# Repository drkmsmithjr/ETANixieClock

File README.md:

# [Estimated Time of Arrival (ETA) Nixie Tube Clock](http://surfncircuits.com/2018/04/01/what-is-an-eta-nixie-tube-clock-and-how-do-you-build-one)
This DIY project will combine the estimated time of arrival function with a nixie tube display to create an estimated time of arrival (ETA) Nixie tube clock. It is all easily controlled by a Raspberry Pi Zero W that is connected to the internet through WiFi to provide the latest time and gets the ETA for any number of destinations. The travel time is provided by the free Google Directions API interface that includes traffic to give the best estimates on any particular day.   The goal is that with an ETA Nixie tube clock, no math is needed to add a rough, often optimistic travel time, to the actual time to determine if we are running late.   The clock does that for you and with the power of IOT, is much more accurate!    A motion sensor is also added to the clock to turn off the Nixie Tube Display when no one is around, saving power and increasing the nixie tube lifetime.    The complete project, including the six IN-4 Nixie tubes, are powered from a 1 amp iPhone charger using the 5v to 170v Nixie Tube Power supply described in another repository. 

See [www.surfncircuits.com](http://surfncircuits.com/2018/04/01/what-is-an-eta-nixie-tube-clock-and-how-do-you-build-one)  for a complete description.  This github repository contains the Kicad Schematic, Spice Simulation, Efficiency Calculations of the Estimated Time of Arrival (ETA) Nixie Tube Clock.   

__ETANixieCode__:  This is the python code that will be placed in the ETANixieClock directory on the Raspberry Pi zero.    

__KC_ETAclock-5v__:  KiCad schematic, PCB Layout, BOM of the ETA Nixie tube clock.  You can order the PCB from oshPark at <a href="https://oshpark.com/shared_projects/B9CmGCXJ"></img></a>  

__SimCalcFiles__:  Spice simulation files of the Nixie Tube bi-quinary driving circuit.    

__Datasheeets__: Datasheets for the pinout and the TPIC6B595.  In the Kicad Schematic, the part numbers and Digikey (TM) links are listed already.   Also the complete BOM is located in the KC-ETAclock-5v Directory (ETAclock_BOM.ods).      

See the complete blogs entry at  [www.surfncircuits.com](http://surfncircuits.com/2018/04/01/what-is-an-eta-nixie-tube-clock-and-how-do-you-build-one)

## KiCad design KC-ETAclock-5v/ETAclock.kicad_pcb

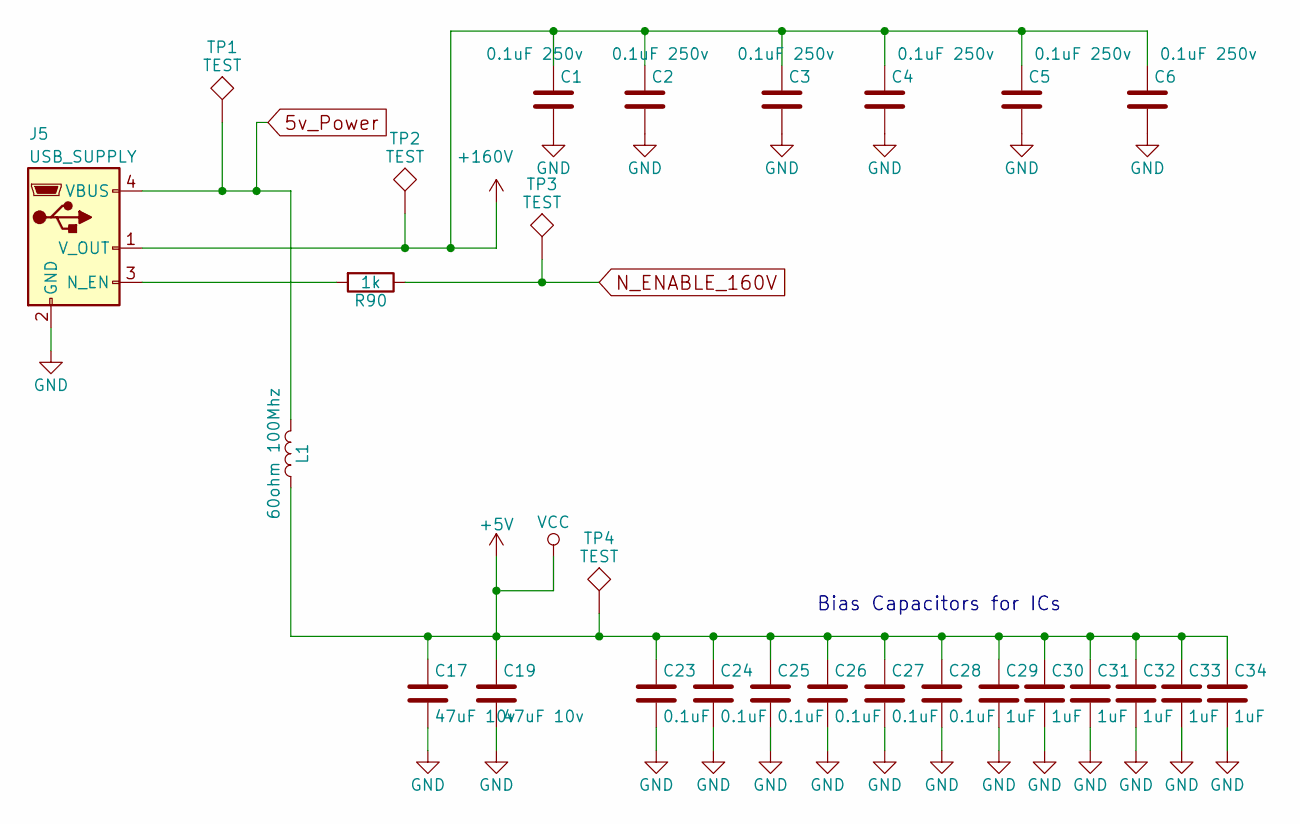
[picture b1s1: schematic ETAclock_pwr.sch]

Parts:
C1, C2, C3, C4, C5, C6: 0.1uF 250v; C_0805; MPN CGA4J3X7T2E104M125AE
C17, C19: 47uF 10v; C_0805; MPN LMK212BBJ476MG-T
C23, C24, C25, C26, C27, C28: 0.1uF; C_0805
C29, C30, C31, C32, C33, C34: 1uF; C_0805
J5: USB_SUPPLY; USB_SUPPLY_5v_TO_170v_MINI_2M
L1: 60ohm 100Mhz; R_0805; MPN BKP2125HS600-T
R90: 1k; R_0805
TP1, TP2, TP3, TP4: TEST; PINTST

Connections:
5v_Power: J5.4 (VBUS), L1.2, TP1.1
+5V: C17.1, C19.1, C23.1, C24.1, C25.1, C26.1, C27.1, C28.1, C29.1, C30.1, C31.1, C32.1, C33.1, C34.1, L1.1, TP4.1; also elsewhere on the board
+160V: C1.1, C2.1, C3.1, C4.1, C5.1, C6.1, J5.1 (V_OUT), TP2.1; also elsewhere on the board
GND: C1.2, C2.2, C3.2, C4.2, C5.2, C6.2, C17.2, C19.2, C23.2, C24.2, C25.2, C26.2, C27.2, C28.2, C29.2, C30.2, C31.2, C32.2, C33.2, C34.2, J5.2 (GND); also elsewhere on the board
N_ENABLE_160V: R90.1, TP3.1; also elsewhere on the board
unnamed: J5.3 (N_EN), R90.2

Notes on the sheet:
Bias Capacitors for ICs

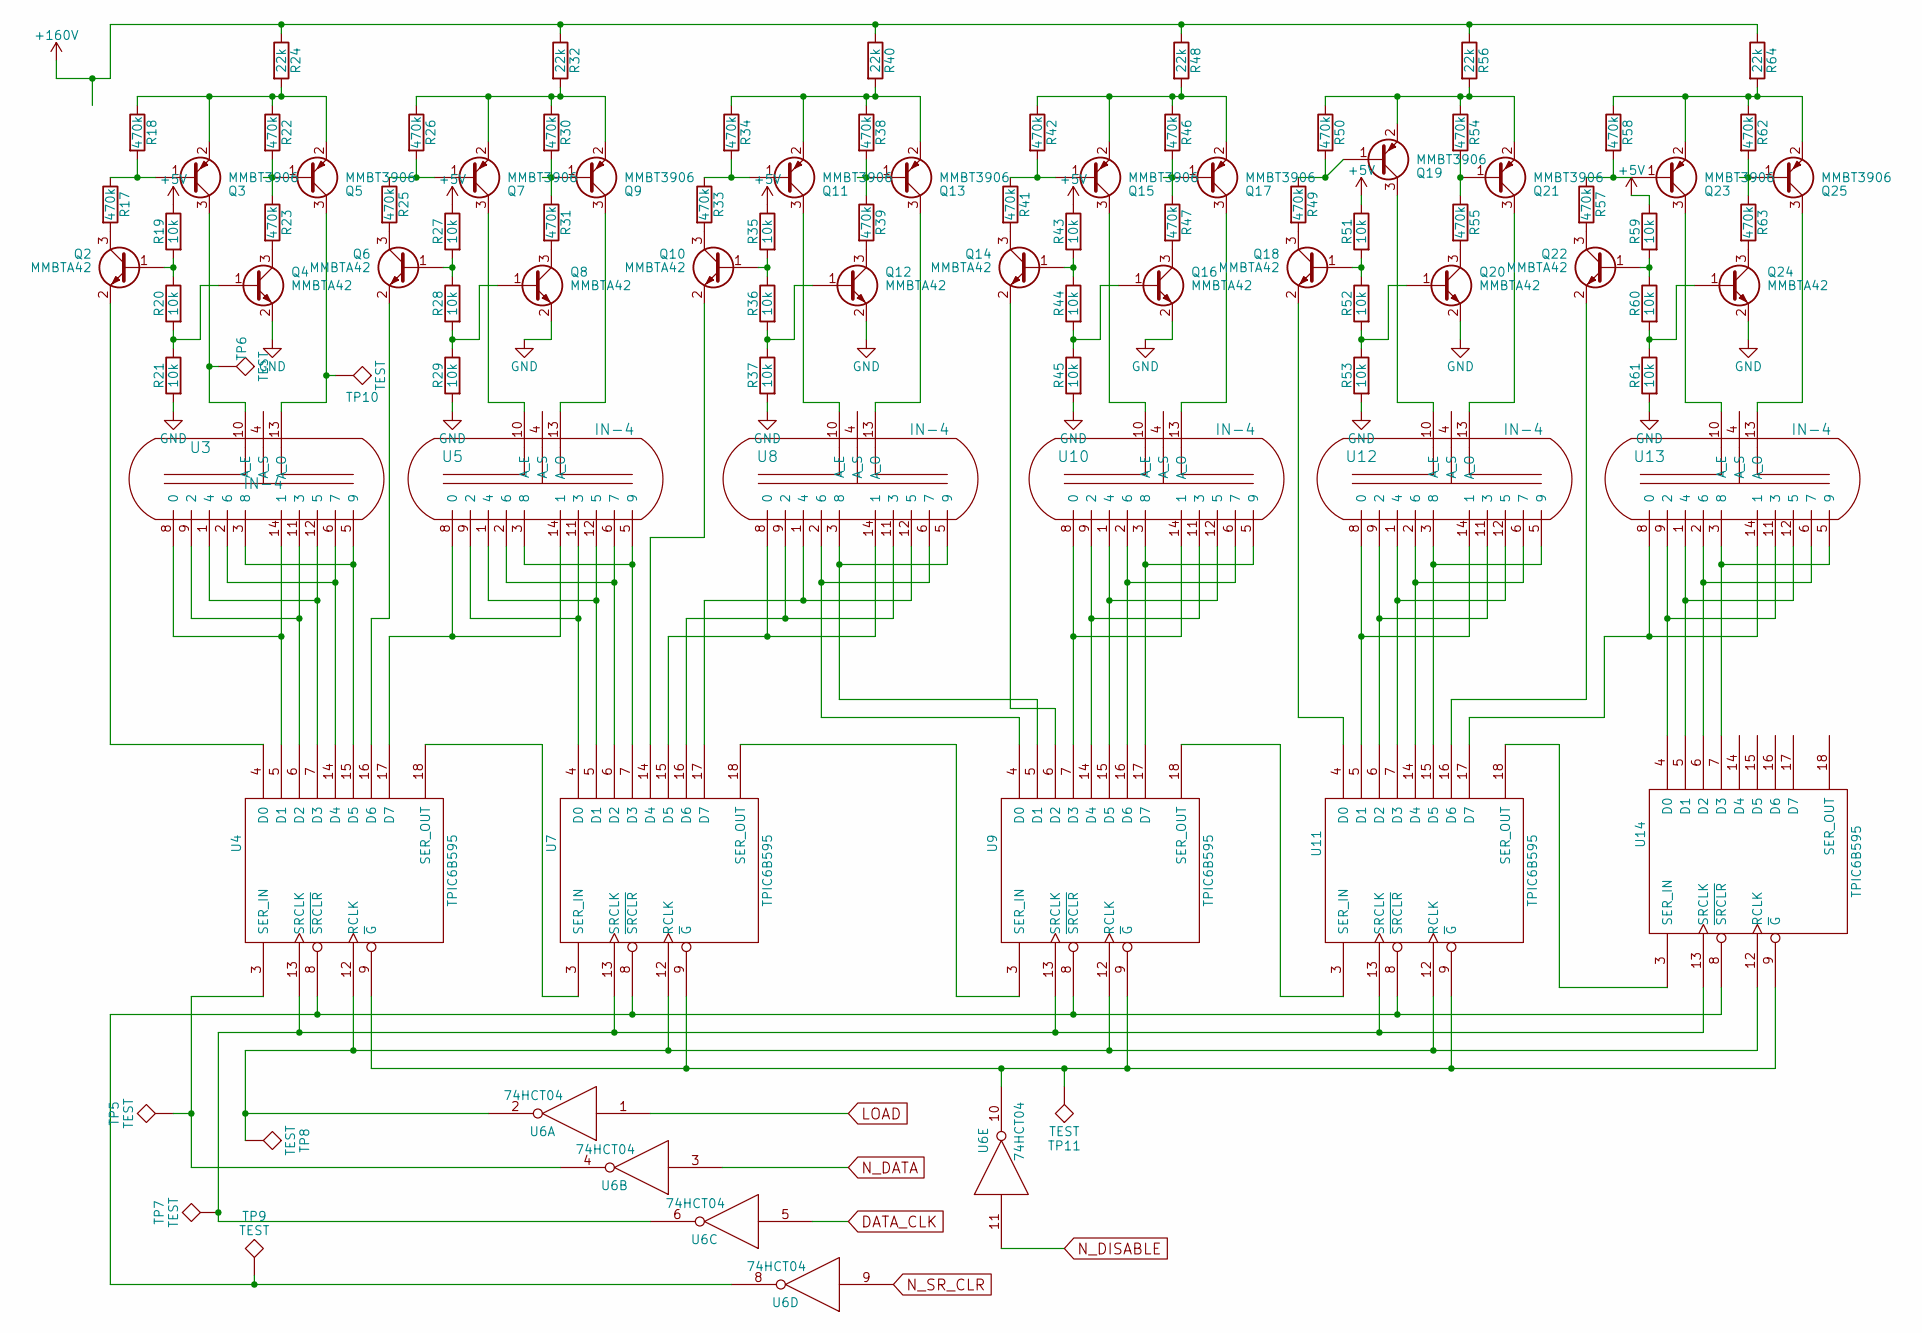
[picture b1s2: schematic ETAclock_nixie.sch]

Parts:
Q2, Q4, Q6, Q8, Q10, Q12, Q14, Q16, Q18, Q20, Q22, Q24: MMBTA42; SOT-23; MPN MMBTA42-TP
Q3, Q5, Q7, Q9, Q11, Q13, Q15, Q17, Q19, Q21, Q23, Q25: MMBT3906; SOT-23; MPN MMBTA92-TP
R17, R18, R22, R23, R25, R26, R30, R31, R33, R34, R38, R39, R41, R42, R46, R47, R49, R50, R54, R55, R57, R58, R62, R63: 470k; R_0805
R19, R20, R21, R27, R28, R29, R35, R36, R37, R43, R44, R45, R51, R52, R53, R59, R60, R61: 10k; R_0805
R24, R32, R40, R48, R56, R64: 22k; R_0805
TP5, TP6, TP7, TP8, TP9, TP10, TP11: TEST; PINTST
U3, U5, U8, U10, U12, U13: IN-4
U4, U7, U9, U11, U14: TPIC6B595; SOIC-20W_7.5x12.8mm_Pitch1.27mm; MPN TPIC6B595DWR
U6: 74HCT04; SOIC-14_3.9x8.7mm_Pitch1.27mm; MPN MM74HCT04MX

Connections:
+5V: R19.1, R27.1, R35.1, R43.1, R51.1, R59.1, U4.2 (VCC), U6.14 (VCC), U7.2 (VCC), U9.2 (VCC), U11.2 (VCC), U14.2 (VCC); also elsewhere on the board
+160V: R24.1, R32.1, R40.1, R48.1, R56.1, R64.1; also elsewhere on the board
DATA_CLK: U6.5; also elsewhere on the board
GND: Q4.2 (E), Q8.2 (E), Q12.2 (E), Q16.2 (E), Q20.2 (E), Q24.2 (E), R21.2, R29.2, R37.2, R45.2, R53.2, R61.2, U4.10 (GND), U4.11 (GND), U4.19 (GND), U6.7 (GND), U7.10 (GND), U7.11 (GND), U7.19 (GND), U9.10 (GND), U9.11 (GND), U9.19 (GND), U11.10 (GND), U11.11 (GND), U11.19 (GND), U14.10 (GND), U14.11 (GND), U14.19 (GND); also elsewhere on the board
LOAD: U6.1; also elsewhere on the board
N_DATA: U6.3; also elsewhere on the board
N_DISABLE: U6.11; also elsewhere on the board
N_SR_CLR: U6.9; also elsewhere on the board
unnamed: Q2.1 (B), R19.2, R20.1
unnamed: Q2.2 (E), U4.4 (D0)
unnamed: Q2.3 (C), R17.2
unnamed: Q3.1 (B), R17.1, R18.2
unnamed: Q3.2 (E), Q5.2 (E), R18.1, R22.1, R24.2
unnamed: Q3.3 (C), TP6.1, U3.10 (A_E)
unnamed: Q4.1 (B), R20.2, R21.1
unnamed: Q4.3 (C), R23.2
unnamed: Q5.1 (B), R22.2, R23.1
unnamed: Q5.3 (C), TP10.1, U3.13 (A_O)
unnamed: Q6.1 (B), R27.2, R28.1
unnamed: Q6.2 (E), U4.16 (D6)
unnamed: Q6.3 (C), R25.2
unnamed: Q7.1 (B), R25.1, R26.2
unnamed: Q7.2 (E), Q9.2 (E), R26.1, R30.1, R32.2
unnamed: Q7.3 (C), U5.10 (A_E)
unnamed: Q8.1 (B), R28.2, R29.1
unnamed: Q8.3 (C), R31.2
unnamed: Q9.1 (B), R30.2, R31.1
unnamed: Q9.3 (C), U5.13 (A_O)
unnamed: Q10.1 (B), R35.2, R36.1
unnamed: Q10.2 (E), U7.14 (D4)
unnamed: Q10.3 (C), R33.2
unnamed: Q11.1 (B), R33.1, R34.2
unnamed: Q11.2 (E), Q13.2 (E), R34.1, R38.1, R40.2
unnamed: Q11.3 (C), U8.10 (A_E)
unnamed: Q12.1 (B), R36.2, R37.1
unnamed: Q12.3 (C), R39.2
unnamed: Q13.1 (B), R38.2, R39.1
unnamed: Q13.3 (C), U8.13 (A_O)
unnamed: Q14.1 (B), R43.2, R44.1
unnamed: Q14.2 (E), U9.6 (D2)
unnamed: Q14.3 (C), R41.2
unnamed: Q15.1 (B), R41.1, R42.2
unnamed: Q15.2 (E), Q17.2 (E), R42.1, R46.1, R48.2
unnamed: Q15.3 (C), U10.10 (A_E)
unnamed: Q16.1 (B), R44.2, R45.1
unnamed: Q16.3 (C), R47.2
unnamed: Q17.1 (B), R46.2, R47.1
unnamed: Q17.3 (C), U10.13 (A_O)
unnamed: Q18.1 (B), R51.2, R52.1
unnamed: Q18.2 (E), U11.4 (D0)
unnamed: Q18.3 (C), R49.2
unnamed: Q19.1 (B), R49.1, R50.2
unnamed: Q19.2 (E), Q21.2 (E), R50.1, R54.1, R56.2
unnamed: Q19.3 (C), U12.10 (A_E)
unnamed: Q20.1 (B), R52.2, R53.1
unnamed: Q20.3 (C), R55.2
unnamed: Q21.1 (B), R54.2, R55.1
unnamed: Q21.3 (C), U12.13 (A_O)
unnamed: Q22.1 (B), R59.2, R60.1
unnamed: Q22.2 (E), U11.16 (D6)
unnamed: Q22.3 (C), R57.2
unnamed: Q23.1 (B), R57.1, R58.2
unnamed: Q23.2 (E), Q25.2 (E), R58.1, R62.1, R64.2
unnamed: Q23.3 (C), U13.10 (A_E)
unnamed: Q24.1 (B), R60.2, R61.1
unnamed: Q24.3 (C), R63.2
unnamed: Q25.1 (B), R62.2, R63.1
unnamed: Q25.3 (C), U13.13 (A_O)
unnamed: TP5.1, U4.3 (SER_IN), U6.4
unnamed: TP7.1, U4.13 (SRCLK), U6.6, U7.13 (SRCLK), U9.13 (SRCLK), U11.13 (SRCLK), U14.13 (SRCLK)
unnamed: TP8.1, U4.12 (RCLK), U6.2, U7.12 (RCLK), U9.12 (RCLK), U11.12 (RCLK), U14.12 (RCLK)
unnamed: TP9.1, U4.8 (~SRCLR), U6.8, U7.8 (~SRCLR), U9.8 (~SRCLR), U11.8 (~SRCLR), U14.8 (~SRCLR)
unnamed: TP11.1, U4.9 (~G), U6.10, U7.9 (~G), U9.9 (~G), U11.9 (~G), U14.9 (~G)
unnamed: U3.1 (4), U3.12 (5), U4.7 (D3)
unnamed: U3.2 (6), U3.6 (7), U4.14 (D4)
unnamed: U3.3 (8), U3.5 (9), U4.15 (D5)
unnamed: U3.9 (2), U3.11 (3), U4.6 (D2)
unnamed: U3.8 (0), U3.14 (1), U4.5 (D1)
unnamed: U4.17 (D7), U5.8 (0), U5.14 (1)
unnamed: U4.18 (SER_OUT), U7.3 (SER_IN)
unnamed: U5.1 (4), U5.12 (5), U7.5 (D1)
unnamed: U5.2 (6), U5.6 (7), U7.6 (D2)
unnamed: U5.3 (8), U5.5 (9), U7.7 (D3)
unnamed: U5.9 (2), U5.11 (3), U7.4 (D0)
unnamed: U7.15 (D5), U8.8 (0), U8.14 (1)
unnamed: U7.16 (D6), U8.9 (2), U8.11 (3)
unnamed: U7.17 (D7), U8.1 (4), U8.12 (5)
unnamed: U7.18 (SER_OUT), U9.3 (SER_IN)
unnamed: U8.2 (6), U8.6 (7), U9.4 (D0)
unnamed: U8.3 (8), U8.5 (9), U9.5 (D1)
unnamed: U9.15 (D5), U10.1 (4), U10.12 (5)
unnamed: U9.16 (D6), U10.2 (6), U10.6 (7)
unnamed: U9.17 (D7), U10.3 (8), U10.5 (9)
unnamed: U9.14 (D4), U10.9 (2), U10.11 (3)
unnamed: U9.7 (D3), U10.8 (0), U10.14 (1)
unnamed: U9.18 (SER_OUT), U11.3 (SER_IN)
unnamed: U11.5 (D1), U12.8 (0), U12.14 (1)
unnamed: U11.6 (D2), U12.9 (2), U12.11 (3)
unnamed: U11.7 (D3), U12.1 (4), U12.12 (5)
unnamed: U11.14 (D4), U12.2 (6), U12.6 (7)
unnamed: U11.15 (D5), U12.3 (8), U12.5 (9)
unnamed: U11.17 (D7), U13.8 (0), U13.14 (1)
unnamed: U11.18 (SER_OUT), U14.3 (SER_IN)
unnamed: U13.1 (4), U13.12 (5), U14.5 (D1)
unnamed: U13.2 (6), U13.6 (7), U14.6 (D2)
unnamed: U13.3 (8), U13.5 (9), U14.7 (D3)
unnamed: U13.9 (2), U13.11 (3), U14.4 (D0)

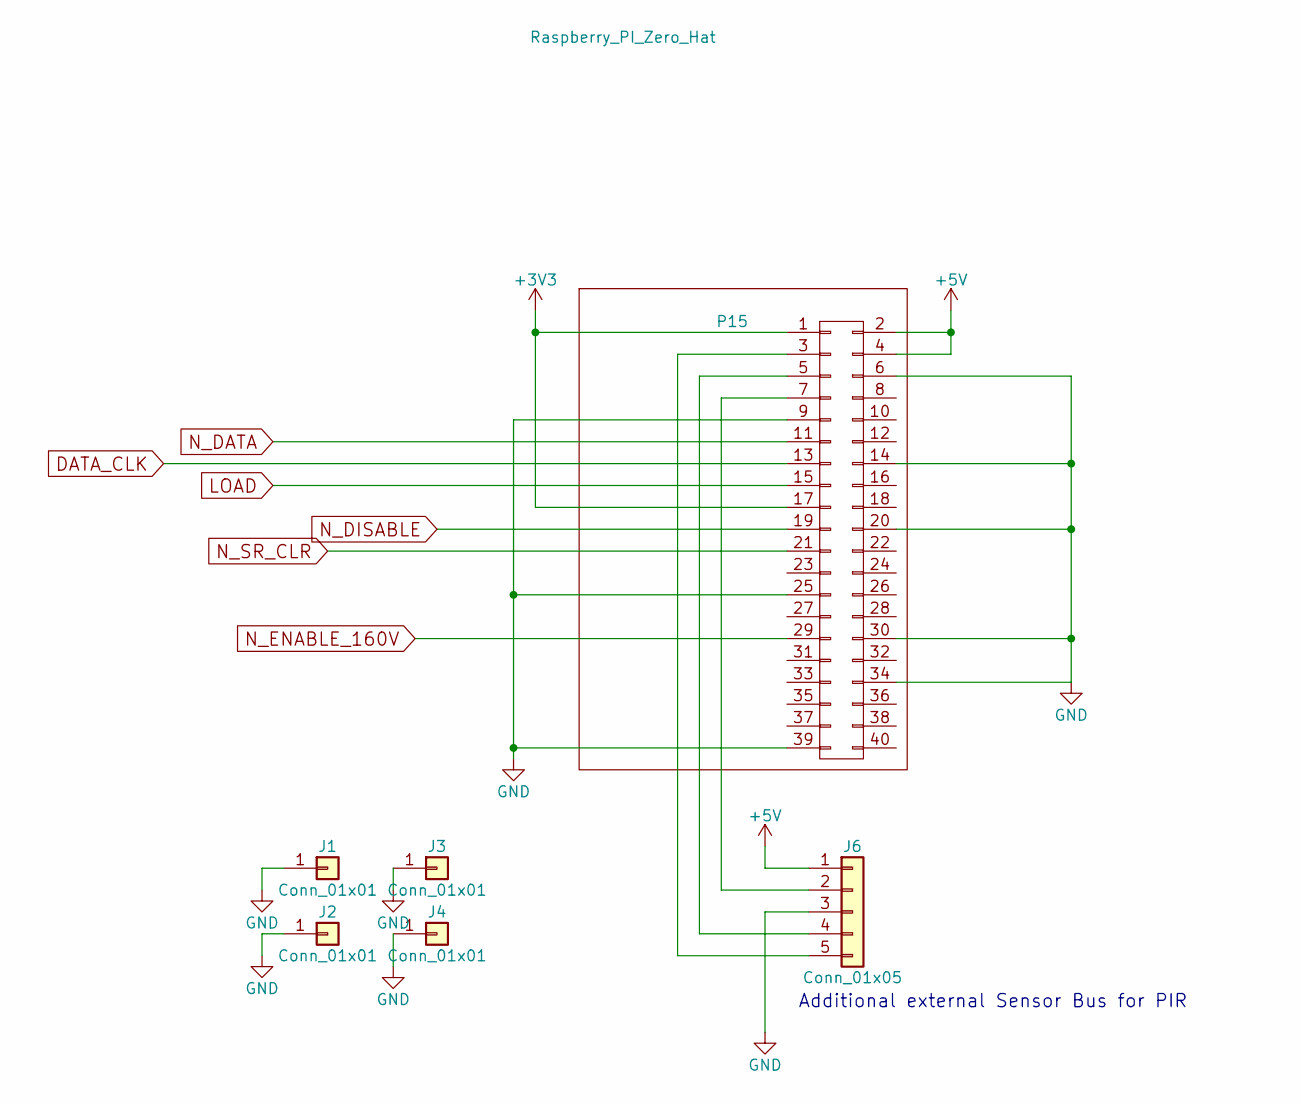
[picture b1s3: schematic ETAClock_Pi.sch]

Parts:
J1, J2, J3, J4: Conn_01x01; MountingHole_2.2mm_M2_Pad
J6: Conn_01x05; Pin_Header_Straight_1x05_Pitch2.54mm
P15: Raspberry_PI_Zero_Hat; R_Pi_Zero_40pins_No_Mount

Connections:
+3V3: P15.1, P15.17
+5V: J6.1, P15.2, P15.4; also elsewhere on the board
DATA_CLK: P15.13; also elsewhere on the board
GND: J1.1, J2.1, J3.1, J4.1, J6.3, P15.6, P15.9, P15.14, P15.20, P15.25, P15.30, P15.34, P15.39; also elsewhere on the board
LOAD: P15.15; also elsewhere on the board
N_DATA: P15.11; also elsewhere on the board
N_DISABLE: P15.19; also elsewhere on the board
N_ENABLE_160V: P15.29; also elsewhere on the board
N_SR_CLR: P15.21; also elsewhere on the board
unnamed: J6.2, P15.7
unnamed: J6.4, P15.5
unnamed: J6.5, P15.3

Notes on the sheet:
Additional external Sensor Bus for PIR

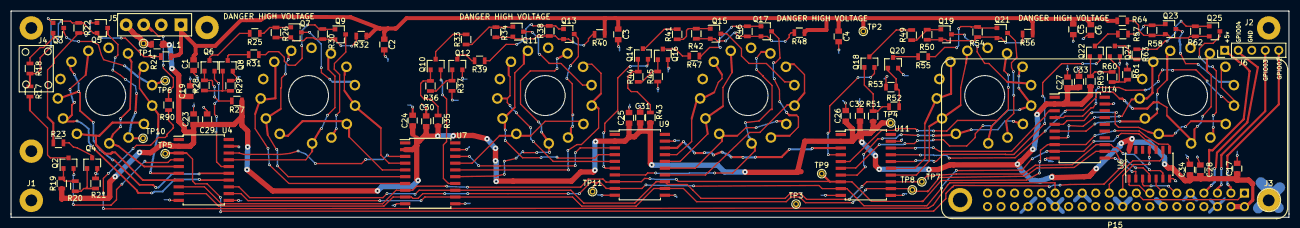
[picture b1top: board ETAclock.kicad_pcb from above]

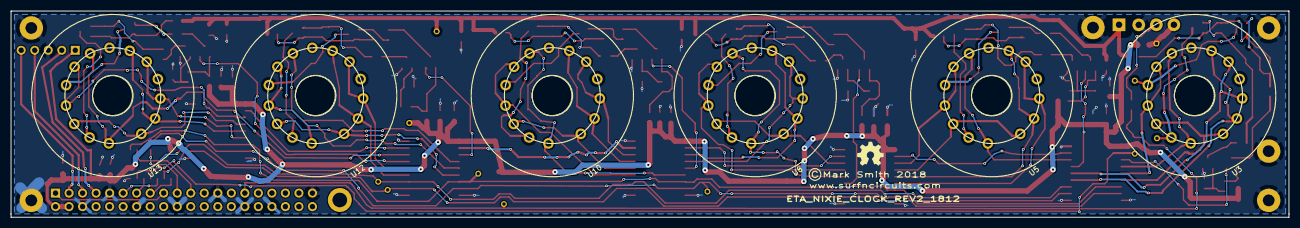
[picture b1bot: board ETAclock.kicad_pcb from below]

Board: 2 copper layers, 240.0 x 38.7 mm, 124 parts (6 on the bottom side), 114 nets.

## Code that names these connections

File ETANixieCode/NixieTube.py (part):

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# the nixie type is for different types of Nixies

# BCM GPIP pin numbers being used 
N_DATA = 17
DATA_CLK = 27
LOAD = 22
N_DISABLE = 10
N_SR_CLR = 9
N_EN_PowerSupply = 5
PIR_SENSE=4

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        # set warnings false to avoid generating errors when the channel was set already
        GPIO.setwarnings(False)
        # intially set N_data high so data is low    
        GPIO.setup(N_DATA,GPIO.OUT, initial=GPIO.HIGH)
        # Data gets shifted in on the falling edge of DATA_CLK
        GPIO.setup(DATA_CLK,GPIO.OUT, initial=GPIO.LOW)
        # The LOAD will transfer shift registers to storge registers on falling edge of LOAD
        GPIO.setup(LOAD,GPIO.OUT , initial=GPIO.LOW)
        # NDISABLE: keeping this low will keep all outputs off on IC 
        self.DISPLAY_ON = False
        GPIO.setup(N_DISABLE,GPIO.OUT , initial=GPIO.LOW)
        # When Low shift registers are transferred to storage registers
        GPIO.setup(N_SR_CLR,GPIO.OUT , initial=GPIO.LOW)
        self.register_clear()
        # pulling low will ENABLE power supply
        self.POWER_ON = False
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     # this will shift the SerialData into the serial registers
     # the data is loaded, then the data_clk goes high then low to clock in 
        for x in self.SerialData:
           GPIO.output(N_DATA, x)
           self.data_clock()
        GPIO.output(N_DATA,GPIO.HIGH)   
           
   def data_clock(self):
        GPIO.output(DATA_CLK,GPIO.HIGH)
        time.sleep(.001)         
        GPIO.output(DATA_CLK,GPIO.LOW)
        
   def LoadData(self):
        GPIO.output(LOAD,GPIO.HIGH)
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        GPIO.output(LOAD,GPIO.LOW)  
        
   def register_clear(self):
        GPIO.output(N_SR_CLR,GPIO.HIGH)
        time.sleep(.001)         
        GPIO.output(N_SR_CLR,GPIO.LOW)
        
   def Display_On(self):
        if self.DISPLAY_ON == False:
           GPIO.output(N_DISABLE,GPIO.HIGH)
           self.DISPLAY_ON = True
   
   def Display_Off(self):
        if self.DISPLAY_ON:
           GPIO.output(N_DISABLE,GPIO.LOW)
           self.DISPLAY_ON = False
           time.sleep(.001)     

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
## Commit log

2018-03-10 Version 1 of the ETA Nixie Tube Clock. This version was ordered from OshPark March 3rd.
2018-03-15 New V2 of Layout to Fix Nixie Tube radius offset and the Nixie tube pin 3 placement. It is suppose to be at 49 degree C instead of 43 degree c.
    Code was updated to add Fade In and Fade Out commands. Also Code updated to
    Add an option for a PIR sensor. The PIR Sensor code is working.
2018-04-01 New Layout changes. Fixed the BJT packages. Added 1k to the 160v_enable pin to protect the rasberry pi. Improved the 160v spacing to the power supply input.
    updated the code with both a testscript and a testETAclock.py to help test the code.
2018-04-01 Added the test bootscript files.
2018-04-01 latest
2018-04-02 cahnged the license to a creative commons Attribute 3.0 for hardware and software sharing
2018-04-02 Updated the readme
2018-04-02 LInk to Oshpark board
2018-04-02 adding a link to the blog in the readme file
2018-04-02 added more the readme
2018-04-02 updatd readme links
2018-04-09 Updated the code to blink the ETA # during ETA display. Also added some new display functions Started the Writeout_spin_to_Digits method, but not finished yet
2018-06-02 The PCB was updated to show FAB lines through the NIXIE tubes so a print copy can be used to make a drill template for the nixie tube cutout.
    The Bom formatting was updated for easy printout.
2018-06-03 Created a new TestDigits.py program to test the Nixie Digits one a time every Three Seconds. This will help to identify if there is any issue with the tubes.
2018-08-07 The TestDigits.py is a script file that allows for the following feastures:
    - cycle through all digits 1 second at a time
    - display any single digit
    - burn in all digits
    - burn in even digits
    - burn in odd digits
    - toggle N_DISABLE
2018-08-16 The testdigits.py script now has more options to help test and debug the nixie tubes. Great for fixing cathode poisoning and for getting all six tubes to work together.
